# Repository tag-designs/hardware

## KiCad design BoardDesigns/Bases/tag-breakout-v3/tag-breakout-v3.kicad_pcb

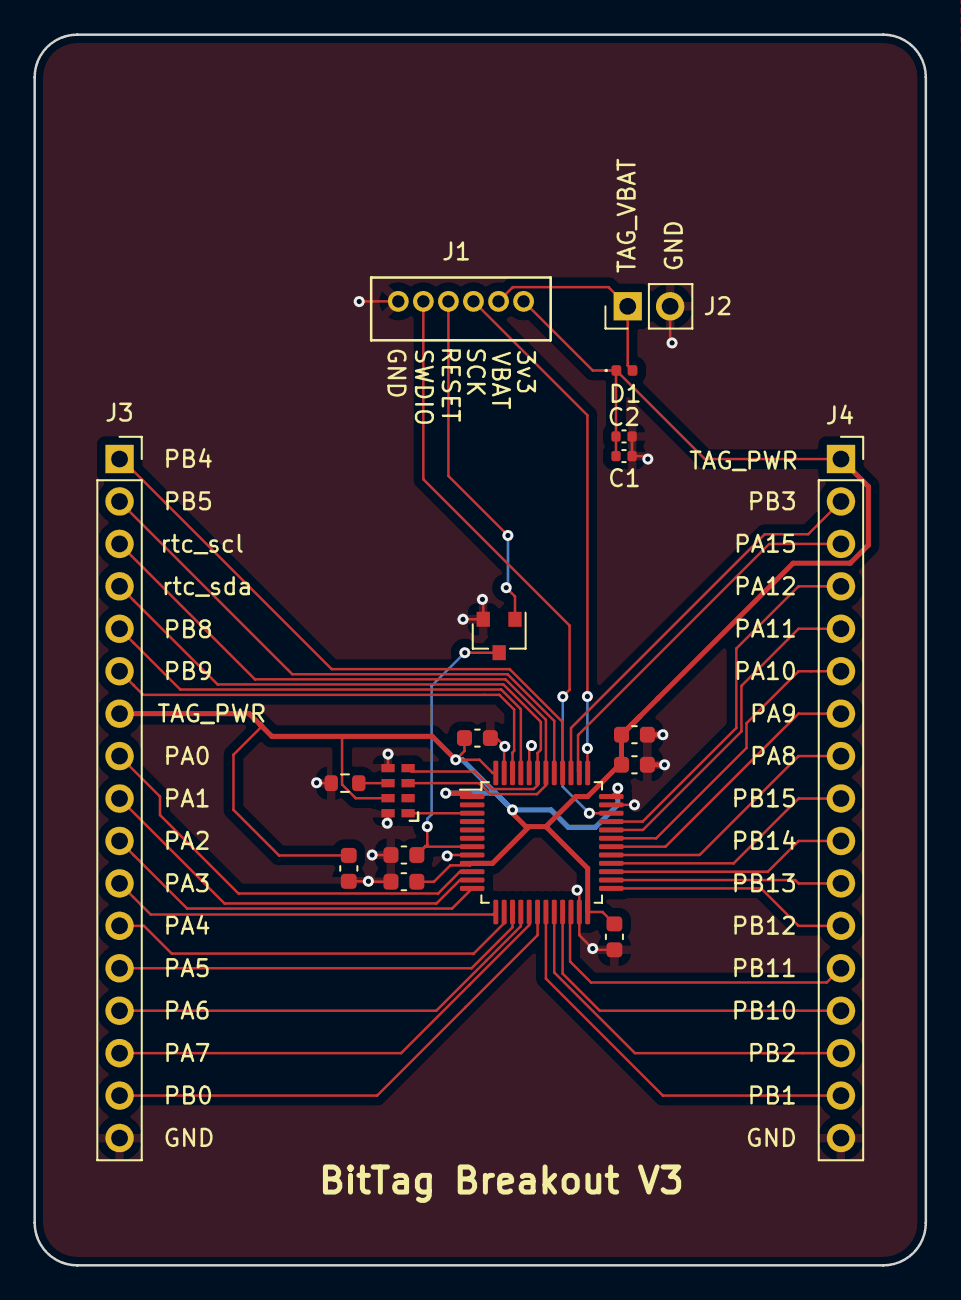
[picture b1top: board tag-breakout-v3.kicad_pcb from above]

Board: 2 copper layers, 53.3 x 73.7 mm, 18 parts (0 on the bottom side), 39 nets.

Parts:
C1, C2: 22uf; C_0402_1005Metric
C3, C4, C5, C6, C7, C9: 0.1uF; C_0603_1608Metric
C10: 4.7uF; C_0603_1608Metric
D1: D; D_0402_1005Metric
J1: Conn_01x06; CONN_B6B-ZR_JST
J2: CONN_01X02; PinHeader_1x02_P2.54mm_Vertical
J3, J4: Conn_01x17; PinSocket_1x17_P2.54mm_Vertical
Q1: Q_NPN_BEC; SOT-23
R3: 10K; R_0603_1608Metric
U6: RV-3028-C7; RV-8803-C7
U7: STM32L431CCTx; LQFP-48_7x7mm_P0.5mm

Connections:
/NRST: C5.1, Q1.3 (C), U7.7 (NRST)
/PA0: J3.8, U7.10 (PA0)
/PA1: J3.9, U7.11 (PA1)
/PA2: J3.10, U7.12 (PA2)
/PA3: J3.11, U7.13 (PA3)
/PA4: J3.12, U7.14 (PA4)
/PA5: J3.13, U7.15 (PA5)
/PA6: J3.14, U7.16 (PA6)
/PA7: J3.15, U7.17 (PA7)
/PA8: J4.8, U7.29 (PA8)
/PA9: J4.7, U7.30 (PA9)
/PA10: J4.6, U7.31 (PA10)
/PA11: J4.5, U7.32 (PA11)
/PA12: J4.4, U7.33 (PA12)
/PA15: J4.3, U7.38 (PA15)
/PB0: J3.16, U7.18 (PB0)
/PB1: J4.16, U7.19 (PB1)
/PB2: J4.15, U7.20 (PB2)
/PB3: J4.2, U7.39 (PB3)
/PB4: J3.1, U7.40 (PB4)
/PB5: J3.2, U7.41 (PB5)
/PB8: J3.5, U7.45 (PB8)
/PB9: J3.6, U7.46 (PB9)
/PB10: J4.14, U7.21 (PB10)
/PB11: J4.13, U7.22 (PB11)
/PB12: J4.12, U7.25 (PB12)
/PB13: J4.11, U7.26 (PB13)
/PB14: J4.10, U7.27 (PB14)
/PB15: J4.9, U7.28 (PB15)
/clkout: U6.1 (CLKOUT), U7.3 (PC14)
/rtc_scl: J3.3, U6.3 (SCL), U7.42 (PB6)
/rtc_sda: J3.4, U6.4 (SDA), U7.43 (PB7)
GND: C1.2, C2.2, C3.2, C4.2, C5.2, C6.2, C7.2, C9.2, C10.2, J1.1, J2.2, J3.17, J4.17, Q1.2 (E), R3.1, U6.5 (GND), U6.8 (EVI), U7.8 (VSSA), U7.23 (VSS), U7.35 (VSS), U7.44 (PH3), U7.47 (VSS)
unnamed: R3.2, U6.6 (VBACK)
TAG_3V3: C1.1, C2.1, C3.1, C4.1, C6.1, C7.1, C9.1, C10.1, D1.1 (K), J1.6, J3.7, J4.1, U6.7 (VDD), U7.1 (VBAT), U7.9 (VDDA), U7.24 (VDD), U7.36 (VDD), U7.48 (VDD)
TAG_RESET: J1.3, Q1.1 (B)
TAG_SCK: J1.4, U7.37 (PA14)
TAG_SWDIO: J1.2, U7.34 (PA13)
TAG_VBAT: D1.2 (A), J1.5, J2.1

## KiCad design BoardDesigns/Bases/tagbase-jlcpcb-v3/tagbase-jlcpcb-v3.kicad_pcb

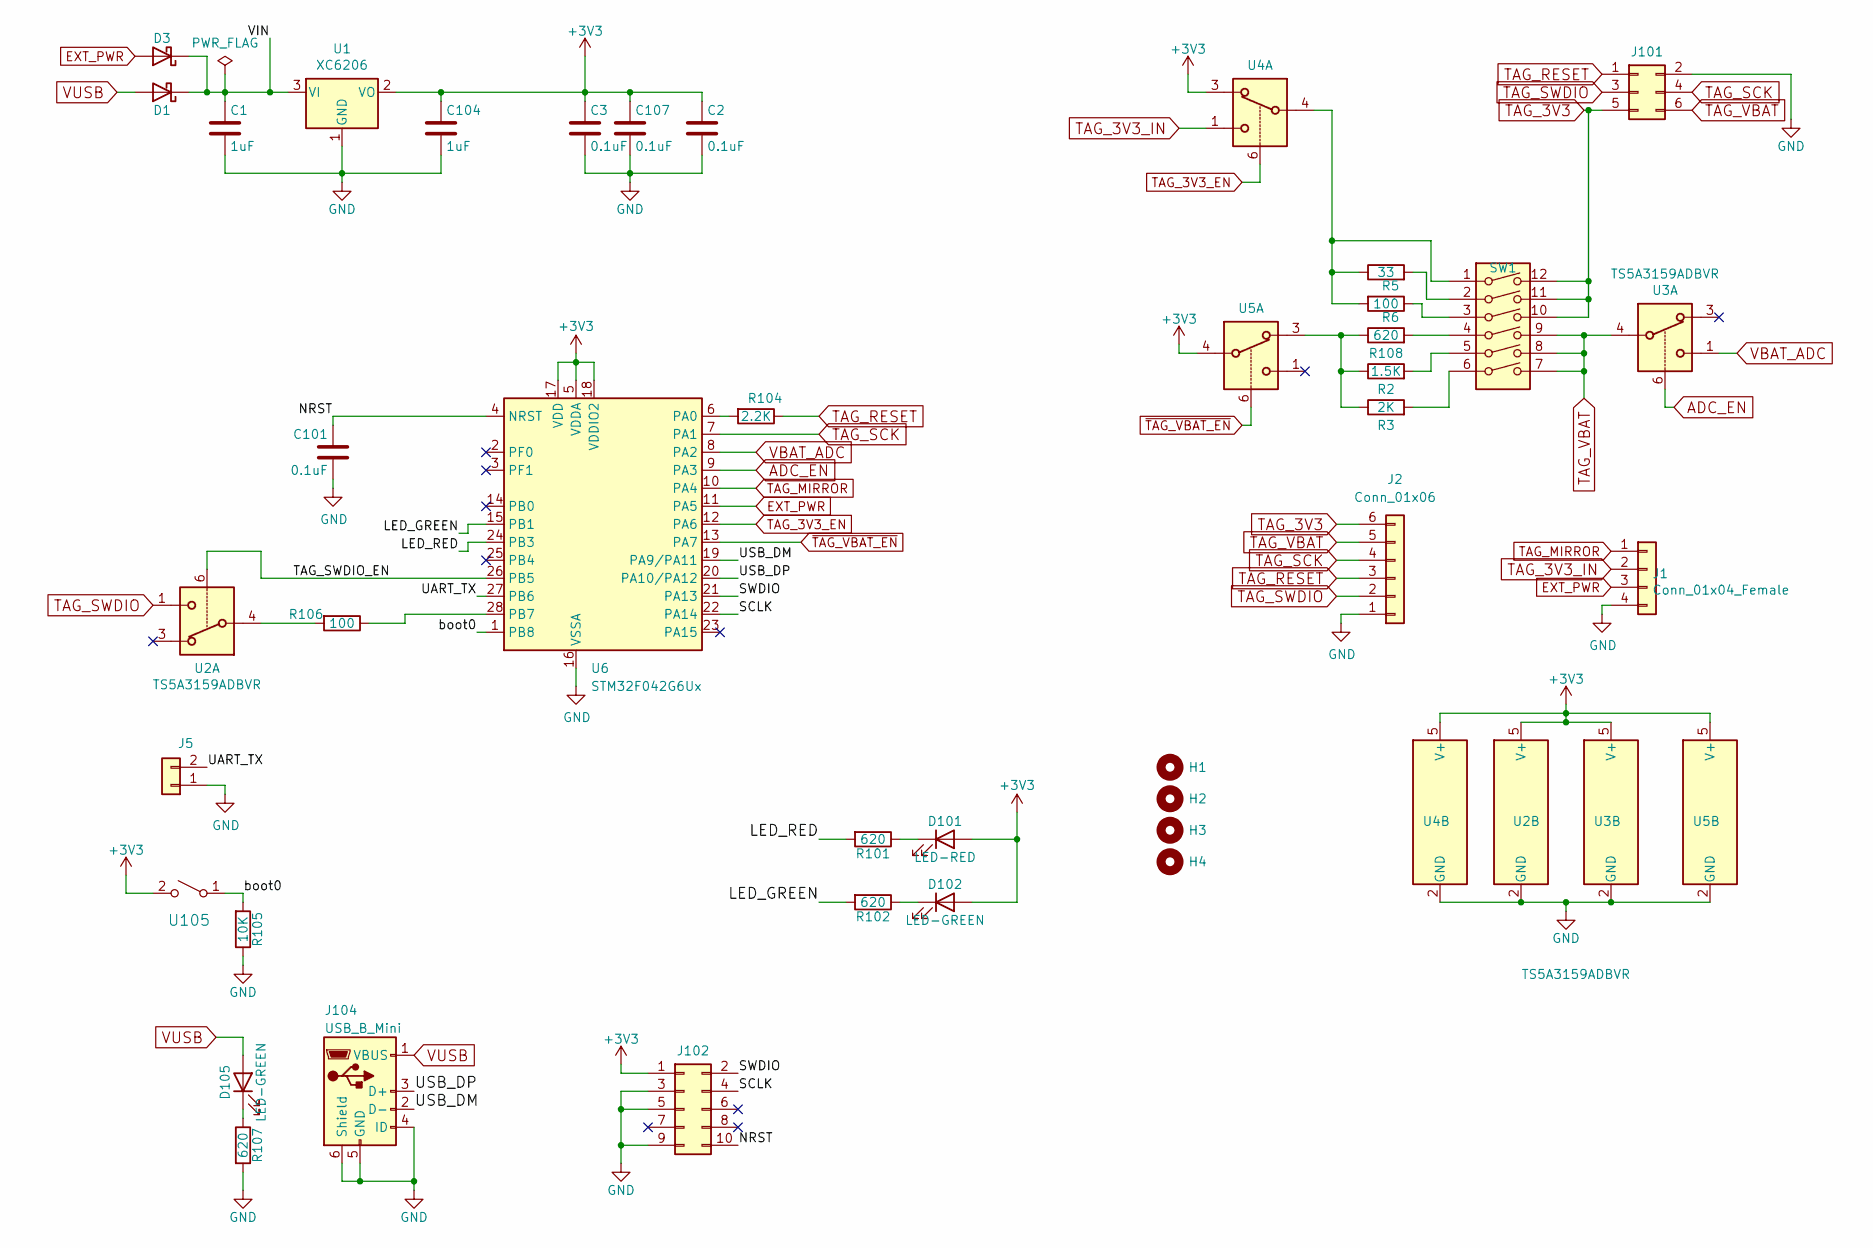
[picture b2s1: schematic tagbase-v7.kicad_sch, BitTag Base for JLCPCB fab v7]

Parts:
C1, C104: 1uF; C_0603_1608Metric; MPN CL10A105KB8NNNC; LCSC C15849
C2, C3, C101, C107: 0.1uF; C_0603_1608Metric; MPN CC0603KRX7R9BB104; LCSC C14663
D1, D3: DIODE; D_SOD-123; MPN B5819W; LCSC C8598
D101: LED-RED; LED_0603_1608Metric; MPN KT-0603R; LCSC C2286
D102, D105: LED-GREEN; LED_0603_1608Metric; MPN 19-217/GHC-YR1S2/3T; LCSC C72043
H1, H2, H3, H4: MountingHole; MountingHole_2.5mm
J1: Conn_01x04_Female; JST_XH_B04B-XH-AM_1x04_P2.50mm_Vertical
J2: Conn_01x06; JST_B6B-ZR(LF)(SN)
J5: Conn_01x02; PinHeader_1x02_P2.54mm_Vertical
J101: Conn_02x03_Odd_Even; 6pin_tagpoints_new_offset
J102: Conn_02x05_Odd_Even; FTSH-105-01-F-D-K
J104: USB_B_Mini; USB_Mini-B; MPN MINI 5PTP; LCSC C2681563
R2: 1.5K; R_0603_1608Metric; MPN 0603WAF1501T5E; LCSC C22843
R3: 2K; R_0603_1608Metric; MPN 0603WAF2001T5E; LCSC C22975
R5: 33; R_0603_1608Metric; MPN 0603WAF330JT5E; LCSC C23140
R6, R106: 100; R_0603_1608Metric; MPN 0603WAF1000T5E; LCSC C22775
R101, R102, R107, R108: 620; R_0603_1608Metric; MPN 0603WAF6200T5E; LCSC C23220
R104: 2.2K; R_0603_1608Metric; MPN 0603WAF1002T5E; LCSC C4190
R105: 10K; R_0603_1608Metric; MPN 0603WAF1002T5E; LCSC C25804
SW1: SW_DIP_x04; SW_DIP_SPSTx06_Slide_KingTek_DSHP06TS_W7.62mm_P1.27mm; MPN DSHP06TSGER; LCSC C3293146
U1: XC6206; SOT-23-3; MPN XC6206P332MR; LCSC C5446
U2, U3, U4, U5: TS5A3159ADBVR; SOT-23-6; MPN TS5A3159ADBVR; LCSC C128405
U6: STM32F042G6Ux; QFN-28_4x4mm_P0.5mm; MPN STM32F042G6U6; LCSC C961597
U105: Tactile Switch; SW_SPST_TS_1187; MPN TS-1187A-C-E-B; LCSC C318889

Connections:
+3V3: C2.1, C3.1, C104.1, C107.1, D101.2 (A), D102.2 (A), J102.1, U1.2 (VO), U2.5 (V+), U3.5 (V+), U4.3, U4.5 (V+), U5.4, U5.5 (V+), U6.5 (VDDA), U6.17 (VDD), U6.18 (VDDIO2), U105.2 (B)
/LED_GREEN: R102.2, U6.15 (PB1)
/LED_RED: R101.2, U6.24 (PB3)
/NRST: C101.1, J102.10, U6.4 (NRST)
/SCLK: J102.4, U6.22 (PA14)
/SWDIO: J102.2, U6.21 (PA13)
/TAG_SWDIO_EN: U2.6, U6.26 (PB5)
/UART_TX: J5.2, U6.27 (PB6)
/USB_DM: J104.2 (D-), U6.19 (PA9/PA11)
/USB_DP: J104.3 (D+), U6.20 (PA10/PA12)
/VIN: C1.1, D1.1 (K), D3.1 (K), U1.3 (VI)
/boot0: R105.2, U6.1 (PB8), U105.1 (A)
ADC_EN: U3.6, U6.9 (PA3)
EXT_PWR: D3.2 (A), J1.3, U6.11 (PA5)
GND: C1.2, C2.2, C3.2, C101.2, C104.2, C107.2, J1.4, J2.1, J5.1, J101.2, J102.3, J102.5, J102.9, J104.4 (ID), J104.5 (GND), J104.6 (Shield), R105.1, R107.2, U1.1 (GND), U2.2 (GND), U3.2 (GND), U4.2 (GND), U5.2 (GND), U6.16 (VSSA)
unnamed: D101.1 (K), R101.1
unnamed: D102.1 (K), R102.1
unnamed: D105.1 (K), R107.1
unnamed: R2.2, SW1.5
unnamed: R3.2, SW1.6
unnamed: R5.1, R6.2, SW1.1, U4.4
unnamed: R5.2, SW1.2
unnamed: R6.1, SW1.3
unnamed: R104.2, U6.6 (PA0)
unnamed: R106.1, U6.28 (PB7)
unnamed: R106.2, U2.4
unnamed: R2.1, R3.1, R108.1, U5.3
unnamed: R108.2, SW1.4
TAG_3V3: J2.6, J101.5, SW1.10, SW1.11, SW1.12
TAG_3V3_EN: U4.6, U6.12 (PA6)
TAG_3V3_IN: J1.2, U4.1
TAG_MIRROR: J1.1, U6.10 (PA4)
TAG_RESET: J2.3, J101.1, R104.1
TAG_SCK: J2.4, J101.4, U6.7 (PA1)
TAG_SWDIO: J2.2, J101.3, U2.1
TAG_VBAT: J2.5, J101.6, SW1.7, SW1.8, SW1.9, U3.4
VBAT_ADC: U3.1, U6.8 (PA2)
VUSB: D1.2 (A), D105.2 (A), J104.1 (VBUS)
~TAG_VBAT_EN: U5.6, U6.13 (PA7)

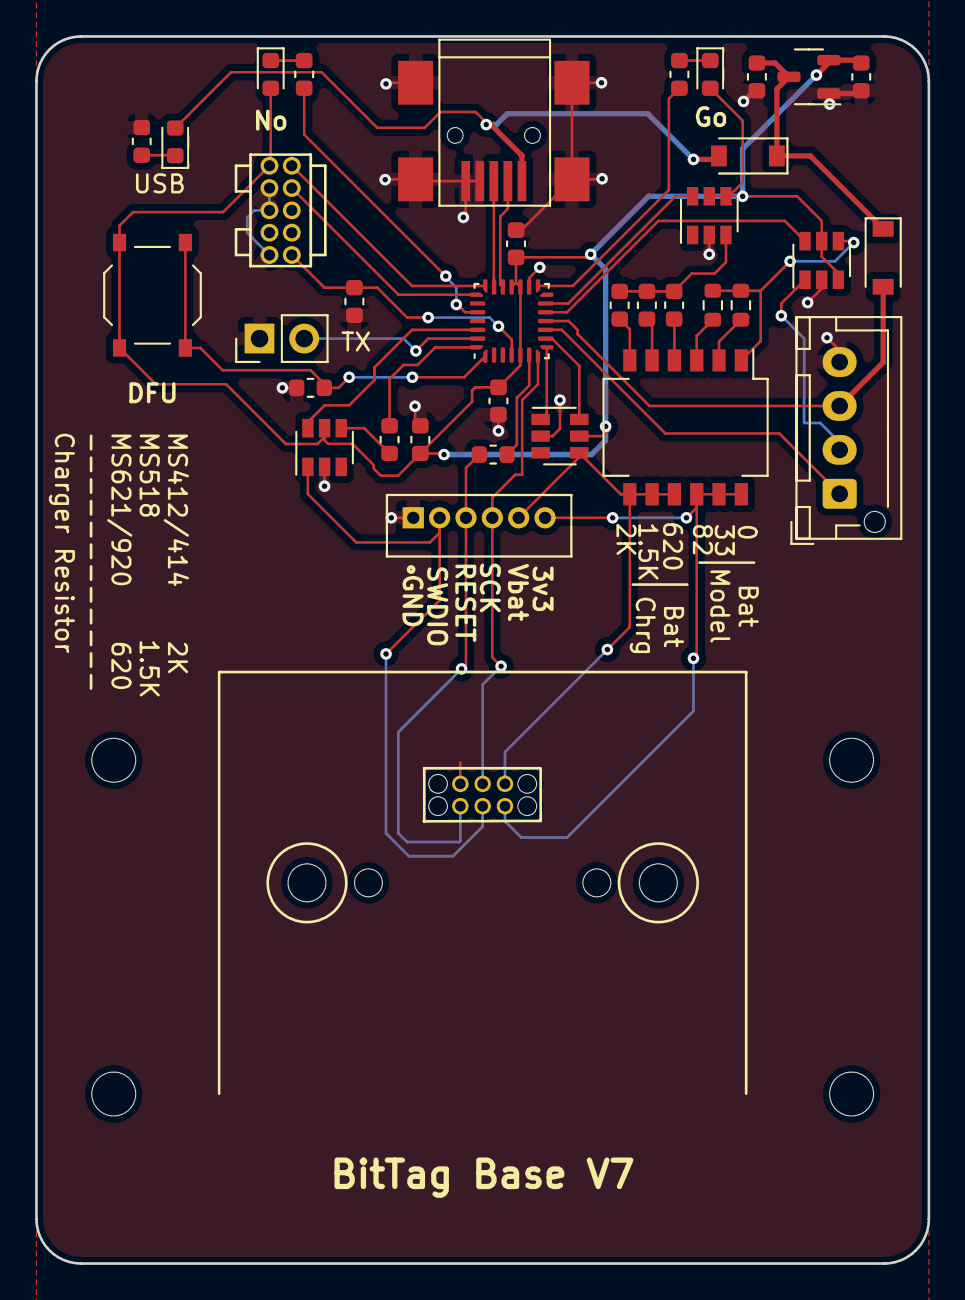
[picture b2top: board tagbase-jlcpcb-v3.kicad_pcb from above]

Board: 2 copper layers, 50.8 x 69.9 mm, 40 parts (0 on the bottom side), 39 nets.

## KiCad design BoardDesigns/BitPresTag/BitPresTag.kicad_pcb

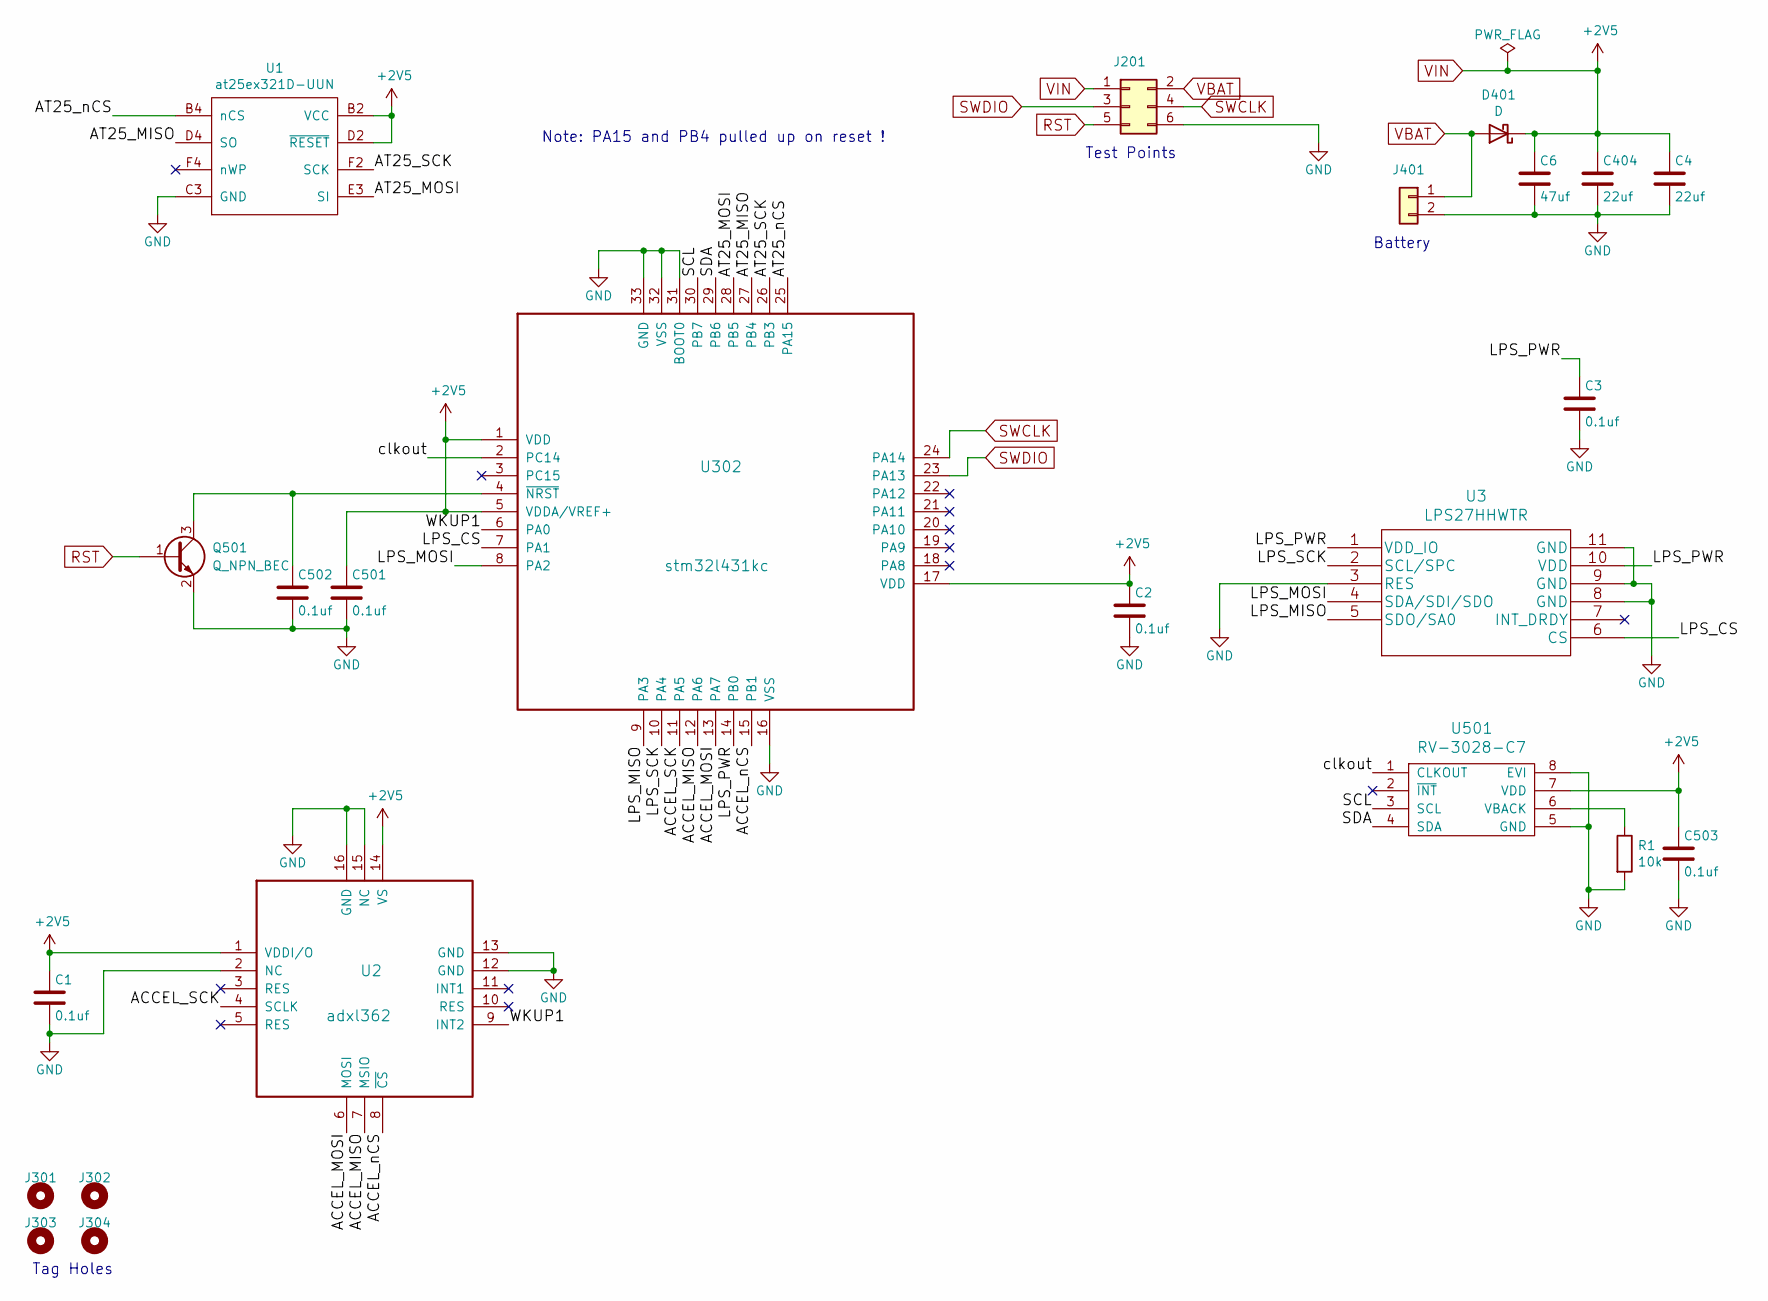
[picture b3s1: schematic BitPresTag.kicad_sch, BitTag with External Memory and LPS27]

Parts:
C1: 0.1uf; C_0201_0603Metric; MPN CL05F104ZO5NNNC
C2: 0.1uf; C_0201_0603Metric; MPN GRM033R60J105MEA2D; LCSC C76929
C3: 0.1uf; C_0201_0603Metric; MPN GRM033C81E104KE14D
C4, C404: 22uf; C_0402_1005Metric; MPN 04026D226MAT2A; LCSC C2179118
C6: 47uf; C_0603_1608Metric; MPN 06036D476MAT2A
C501, C502, C503: 0.1uf; C_0201_0603Metric; MPN C181047; LCSC C181047
D401: D; D_0402_1005Metric; MPN CDBQC0130L-HF; LCSC C2886012
J201: CONN_02X04; tagpoints6
J301, J302, J303, J304: Conn_01x01; taghole1.1mm
J401: CONN_01X02; MS621
Q501: Q_NPN_BEC; SOT-883; MPN BC847AMB,315; LCSC C686658
R1: 10k; R_0201_0603Metric; MPN RC0201FR-0710KL; LCSC C106225
U1: at25ex321D-UUN; adesto_wlcsp12; MPN AT25FF321A-UUN-T; LCSC C1858339
U2: adxl362; ADXL362; MPN ADXL362BCCZ-RL7
U3: LPS27HHWTR; MPN LPS27HHTWTR
U302: stm32l431kc; QFN-32-1EP_5x5mm_P0.5mm_EP3.45x3.45mm; MPN STM32L432KCU6; LCSC C1337280
U501: RV-3028-C7; RV-8803-C7; MPN RV-3028-C7 32.768KHZ 1PPM-TA-QA; LCSC C3019759

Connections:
/ACCEL_MISO: U2.7 (MSIO), U302.12 (PA6)
/ACCEL_MOSI: U2.6 (MOSI), U302.13 (PA7)
/ACCEL_SCK: U2.4 (SCLK), U302.11 (PA5)
/ACCEL_nCS: U2.8 (~CS), U302.15 (PB1)
/AT25_MISO: U1.D4 (SO), U302.27 (PB4)
/AT25_MOSI: U1.E3 (SI), U302.28 (PB5)
/AT25_SCK: U1.F2 (SCK), U302.26 (PB3)
/AT25_nCS: U1.B4 (nCS), U302.25 (PA15)
/LPS_CS: U3.6 (CS), U302.7 (PA1)
/LPS_MISO: U3.5 (SDO/SA0), U302.9 (PA3)
/LPS_MOSI: U3.4 (SDA/SDI/SDO), U302.8 (PA2)
/LPS_PWR: C3.1, U3.1 (VDD_IO), U3.10 (VDD), U302.14 (PB0)
/LPS_SCK: U3.2 (SCL/SPC), U302.10 (PA4)
/SCL: U302.30 (PB7), U501.3 (SCL)
/SDA: U302.29 (PB6), U501.4 (SDA)
/WKUP1: U2.9 (INT2), U302.6 (PA0)
/clkout: U302.2 (PC14), U501.1 (CLKOUT)
GND: C1.2, C2.2, C3.2, C4.2, C6.2, C404.2, C501.2, C502.2, C503.2, J201.6, J401.2, Q501.2 (E), R1.2, U1.C3 (GND), U2.2 (NC), U2.12 (GND), U2.13 (GND), U2.15 (NC), U2.16 (GND), U3.3 (RES), U3.8 (GND), U3.9 (GND), U3.11 (GND), U302.16 (VSS), U302.31 (BOOT0), U302.32 (VSS), U302.33 (GND), U501.5 (GND), U501.8 (EVI)
unnamed: C502.1, Q501.3 (C), U302.4 (~NRST)
unnamed: R1.1, U501.6 (VBACK)
RST: J201.5, Q501.1 (B)
SWCLK: J201.4, U302.24 (PA14)
SWDIO: J201.3, U302.23 (PA13)
VBAT: D401.2 (A), J201.2, J401.1
VIN: C1.1, C2.1, C4.1, C6.1, C404.1, C501.1, C503.1, D401.1 (K), J201.1, U1.B2 (VCC), U1.D2 (~RESET), U2.1 (VDDI/O), U2.14 (VS), U302.1 (VDD), U302.5 (VDDA/VREF+), U302.17 (VDD), U501.7 (VDD)

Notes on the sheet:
Note: PA15 and PB4 pulled up on reset !
Tag Holes
Test Points
Battery

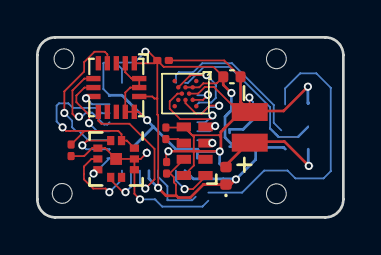
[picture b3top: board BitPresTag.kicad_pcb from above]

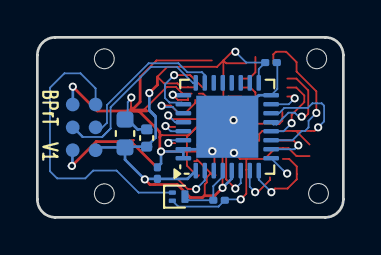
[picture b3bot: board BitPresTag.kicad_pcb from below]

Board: 2 copper layers, 17.0 x 10.0 mm, 23 parts (8 on the bottom side), 25 nets.

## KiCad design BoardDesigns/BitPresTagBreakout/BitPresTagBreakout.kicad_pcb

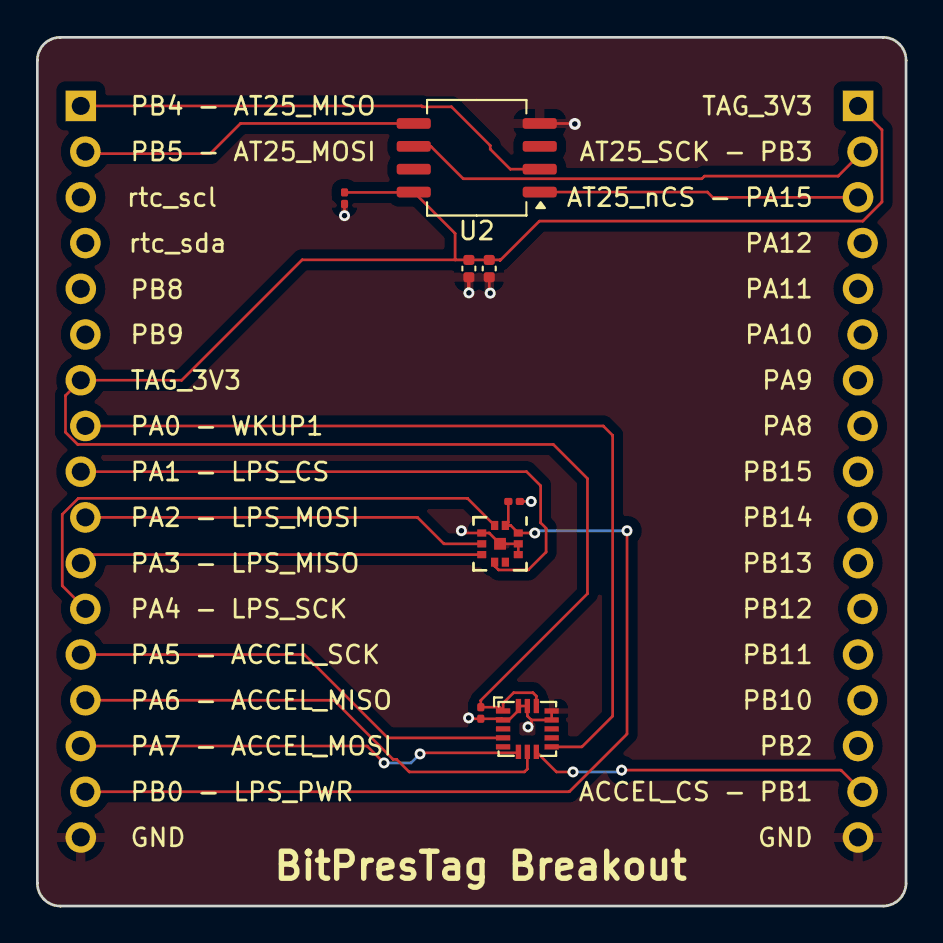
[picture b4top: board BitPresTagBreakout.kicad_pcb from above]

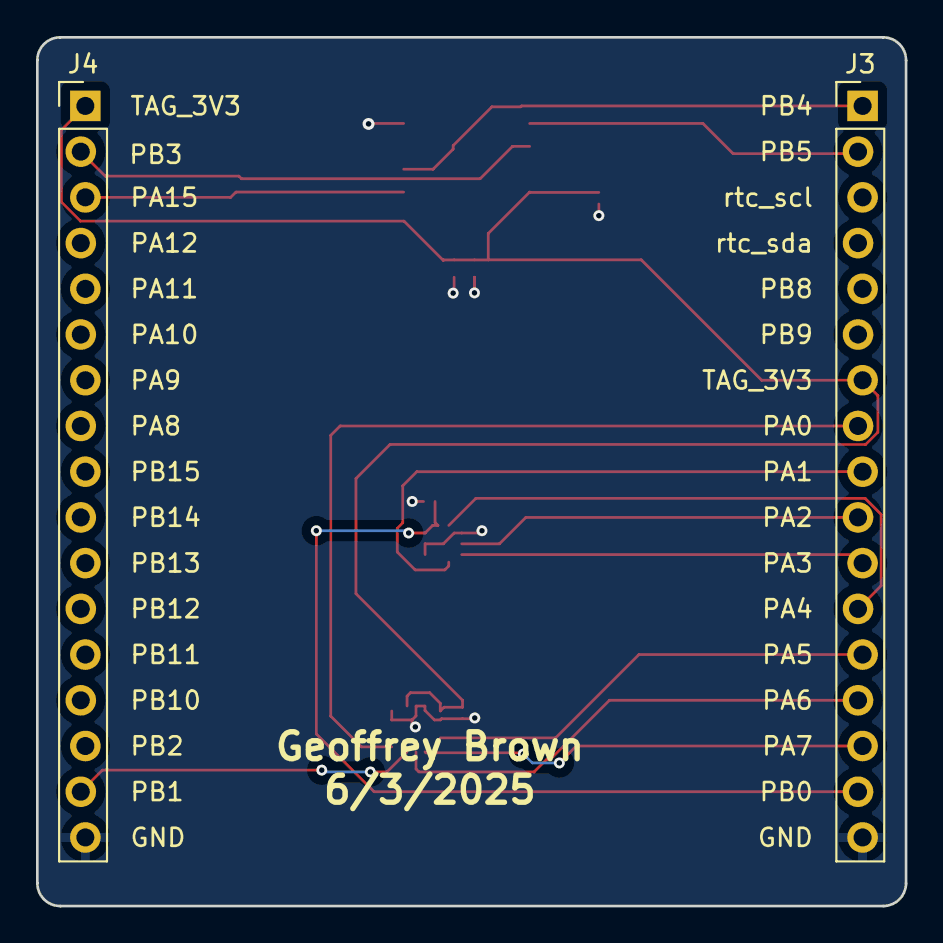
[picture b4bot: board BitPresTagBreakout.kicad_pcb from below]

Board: 2 copper layers, 48.3 x 48.3 mm, 10 parts (2 on the bottom side), 16 nets.

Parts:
C1, C2: 0.1uf; C_0201_0603Metric
C9: 1uf; C_0201_0603Metric
C10, C11: 22uf; C_0402_1005Metric
J3, J4: Conn_01x17; PinHeader_1x17_P2.54mm_Vertical_Staggered
U2: AT25XE321; SO-8_5.3x6.2mm_P1.27mm
U3: LPS27HHWTR
U4: adxl362; ADXL362

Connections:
/ACCEL_MISO: J3.14, U4.7 (MSIO)
/ACCEL_MOSI: J3.15, U4.6 (MOSI)
/ACCEL_SCK: J3.13, U4.4 (SCLK)
/ACCEL_nCS: J4.16, U4.8 (~CS)
/AT25_MISO: J3.1, U2.2 (SIO1)
/AT25_MOSI: J3.2, U2.5 (SIO0)
/AT25_SCK: J4.2, U2.6 (SCLK)
/AT25_nCS: J4.3, U2.1 (nCS)
/LPS_CS: J3.9, U3.6 (CS)
/LPS_MISO: J3.11, U3.5 (SDO/SA0)
/LPS_MOSI: J3.10, U3.4 (SDA/SDI/SDO)
/LPS_PWR: C1.1, J3.16, U3.1 (VDD_IO), U3.10 (VDD)
/LPS_SCK: J3.12, U3.2 (SCL/SPC)
/TAG_3V3: C2.1, C9.1, C10.1, C11.1, J3.7, J4.1, U2.8 (VCC), U4.1 (VDDI/O), U4.14 (VS)
/WKUP1: J3.8, U4.9 (INT2)
GND: C1.2, C2.2, C9.2, C10.2, C11.2, J3.17, J4.17, U2.4 (GND), U3.3 (RES), U3.8 (GND), U3.9 (GND), U3.11 (GND), U4.2 (NC), U4.12 (GND), U4.13 (GND), U4.15 (NC), U4.16 (GND)

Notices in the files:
parts and their libraries:
Copyright 2016 Accelerated Designs. All rights reserved.
